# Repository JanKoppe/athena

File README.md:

# Athena

_2.1 audio crossover and headphone amplifier_

This is a work-in-progress on a simple 2.1 audio crossover using active 2nd-order RC filters, as well as a headphone amplifier based on the popular CMoy design. The PCBs have not yet been ordered and confirmed.

## Crossover frequency

The crossover frequency is set by the resistors R11-R16 and the capacitors C5-C10. Keep the values for all components the same.

Using a fixed, commonly available 100nF capacitor the following (and more) corner frequencies can be set:

Resistance | Frequency
-----------|----------
22 kOhms   |  72,34 Hz
20 kOhms   |  79,57 Hz
18 kOhms   |  88,42 Hz
16 kOhms   |  99,47 Hz
15 kOhms   | 106,10 Hz
13 kOhms   | 122,48 Hz
12 kOhms   | 132,64 Hz

## Power supply

The unit should be powered by at least 12 volts DC, but no more than 30 volts DC. More voltage will give you higher headroom for greater amplification (headphone) and high-level signal handling, though you should be able to use a regular 12 volts DC power supply for consumer line levels.

__Attention:__ The power supply must _never_ be connected to signal ground because this schematic referencing ground to VCC/2, i.e. the power supply ground is actually the negative voltage rail. Using a wall wart power supply you should not run into any issues. This avoids adding large capacitors in series on the outputs.

## Enclosure

Use Fischer Elektronik KOH-1100 and KOH-2100 case components with lasercut panels from 2mm plexiglas for the enclosure. CAD files for panel cutouts are included.

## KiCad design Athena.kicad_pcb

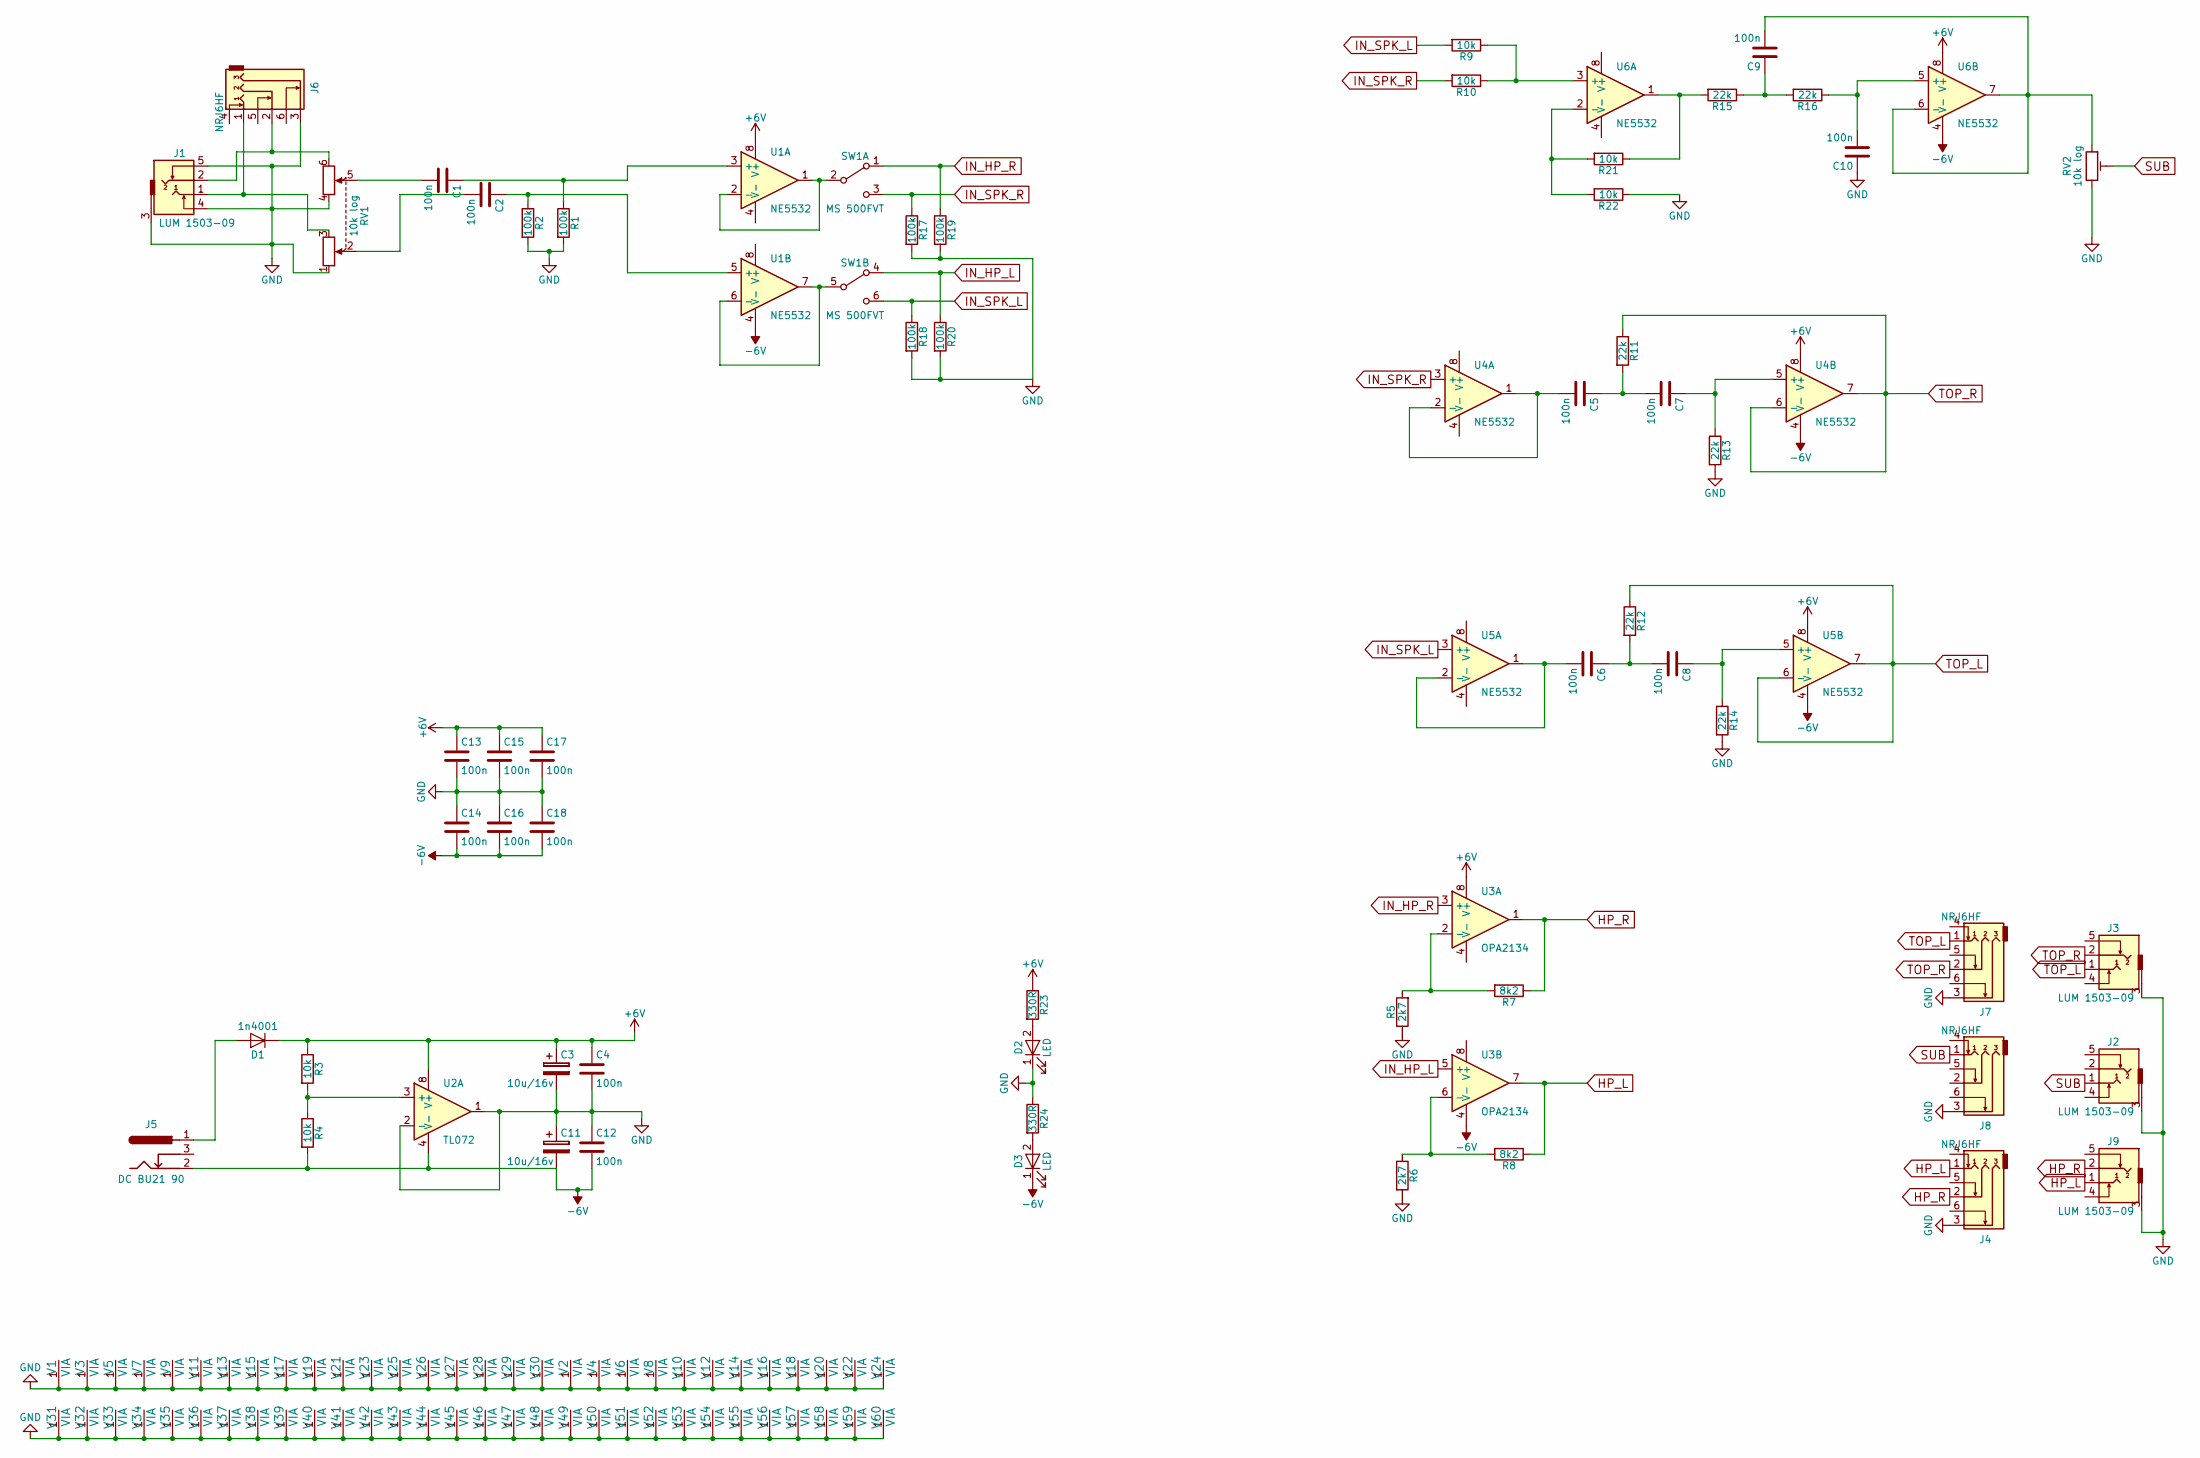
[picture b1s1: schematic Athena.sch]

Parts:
C1, C2, C4, C5, C6, C7, C8, C9, C10, C12, C13, C14, C15, C16, C17, C18: 100n; C_0805_HandSoldering
C3, C11: 10u/16v; CP_Elec_4x5.3
D1: 1n4001; D_DO-41_SOD81_P7.62mm_Horizontal
D2: LED; LED_D3.0mm_Horizontal_O3.81mm_Z6.0mm
D3: LED; LED_D3.0mm_Horizontal_O1.27mm_Z2.0mm
J1, J2, J3, J9: LUM 1503-09; LUM1503-09
J4, J6, J7, J8: NRJ6HF
J5: DC BU21 90; BARREL_JACK
R1, R2, R17, R18, R19, R20: 100k; R_0603_HandSoldering
R3, R4, R9, R10, R21, R22: 10k; R_0603_HandSoldering
R5, R6: 2k7; R_0603_HandSoldering
R7, R8: 8k2; R_0603_HandSoldering
R11, R12, R13, R14, R15, R16: 22k; R_0603_HandSoldering
R23, R24: 330R; R_0603_HandSoldering
RV1: 10k log; Potentiometer_Alps_RK09L_Double_Vertical
RV2: 10k log; Potentiometer_Trimmer_ACP_CA6v_Horizontal
SW1: MS 500FVT; MS500FVT
U1, U4, U5, U6: NE5532; SOIC-8_3.9x4.9mm_Pitch1.27mm
U2: TL072; SOIC-8_3.9x4.9mm_Pitch1.27mm
U3: OPA2134; SOIC-8_3.9x4.9mm_Pitch1.27mm
V1, V2, V3, V4, V5, V6, V7, V8, V9, V10, V11, V12, V13, V14, V15, V16, V17, V18, V19, V20, V21, V22, V23, V24, V25, V26, V27, V28, V29, V30, V31, V32, V33, V34, V35, V36, V37, V38, V39, V40, V41, V42, V43, V44, V45, V46, V47, V48, V49, V50, V51, V52, V53, V54, V55, V56, V57, V58, V59, V60: VIA; VIA-0.6

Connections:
+6V: C3.1, C4.1, C13.1, C15.1, C17.1, D1.1 (K), R3.1, R23.1, U1.8 (V+), U2.8 (V+), U3.8 (V+), U4.8 (V+), U5.8 (V+), U6.8 (V+)
-6V: C11.2, C12.2, C14.2, C16.2, C18.2, D3.1 (K), J5.2, R4.2, U1.4 (V-), U2.4 (V-), U3.4 (V-), U4.4 (V-), U5.4 (V-), U6.4 (V-)
GND: C3.2, C4.2, C10.1, C11.1, C12.1, C13.2, C14.1, C15.2, C16.1, C17.2, C18.1, D2.1 (K), J1.3, J1.4, J1.5, J2.3, J3.3, J4.3, J6.3, J7.3, J8.3, J9.3, R1.2, R2.2, R5.1, R6.2, R13.2, R14.2, R17.2, R18.2, R19.2, R20.2, R22.1, R24.1, RV1.0, RV1.1, RV1.4, RV2.3, U2.1, U2.2 (-), V1.1, V2.1, V3.1, V4.1, V5.1, V6.1, V7.1, V8.1, V9.1, V10.1, V11.1, V12.1, V13.1, V14.1, V15.1, V16.1, V17.1, V18.1, V19.1, V20.1, V21.1, V22.1, V23.1, V24.1, V25.1, V26.1, V27.1, V28.1, V29.1, V30.1, V31.1, V32.1, V33.1, V34.1, V35.1, V36.1, V37.1, V38.1, V39.1, V40.1, V41.1, V42.1, V43.1, V44.1, V45.1, V46.1, V47.1, V48.1, V49.1, V50.1, V51.1, V52.1, V53.1, V54.1, V55.1, V56.1, V57.1, V58.1, V59.1, V60.1; also elsewhere on the board
HP_L: J4.1, J9.1, R8.1, U3.7
HP_R: J4.2, J9.2, R7.1, U3.1
IN_HP_L: R20.1, SW1.4 (A), U3.5 (+)
IN_HP_R: R19.1, SW1.1 (A), U3.3 (+)
IN_SPK_L: R9.2, R18.1, SW1.6 (C), U5.3 (+)
IN_SPK_R: R10.2, R17.1, SW1.3 (C), U4.3 (+)
unnamed: C1.1, R1.1, U1.3 (+)
unnamed: C1.2, RV1.5
unnamed: C2.1, R2.1, U1.5 (+)
unnamed: C2.2, RV1.2
unnamed: C5.1, C7.2, R11.2
unnamed: C5.2, U4.1, U4.2 (-)
unnamed: C6.1, C8.2, R12.2
unnamed: C6.2, U5.1, U5.2 (-)
unnamed: C7.1, R13.1, U4.5 (+)
unnamed: C8.1, R14.1, U5.5 (+)
unnamed: C9.1, R15.1, R16.2
unnamed: C9.2, RV2.1, U6.6 (-), U6.7
unnamed: C10.2, R16.1, U6.5 (+)
unnamed: D1.2 (A), J5.1
unnamed: D2.2 (A), R23.2
unnamed: D3.2 (A), R24.2
unnamed: J1.1, J6.1, RV1.3
unnamed: J1.2, J6.2, RV1.6
unnamed: R3.2, R4.1, U2.3 (+)
unnamed: R5.2, R7.2, U3.2 (-)
unnamed: R6.1, R8.2, U3.6 (-)
unnamed: R9.1, R10.1, U6.3 (+)
unnamed: R15.2, R21.1, U6.1
unnamed: R21.2, R22.2, U6.2 (-)
unnamed: SW1.2 (B), U1.1, U1.2 (-)
unnamed: SW1.5 (B), U1.6 (-), U1.7
SUB: J2.1, J8.1, RV2.2
TOP_L: J3.1, J7.1, R12.1, U5.6 (-), U5.7
TOP_R: J3.2, J7.2, R11.1, U4.6 (-), U4.7

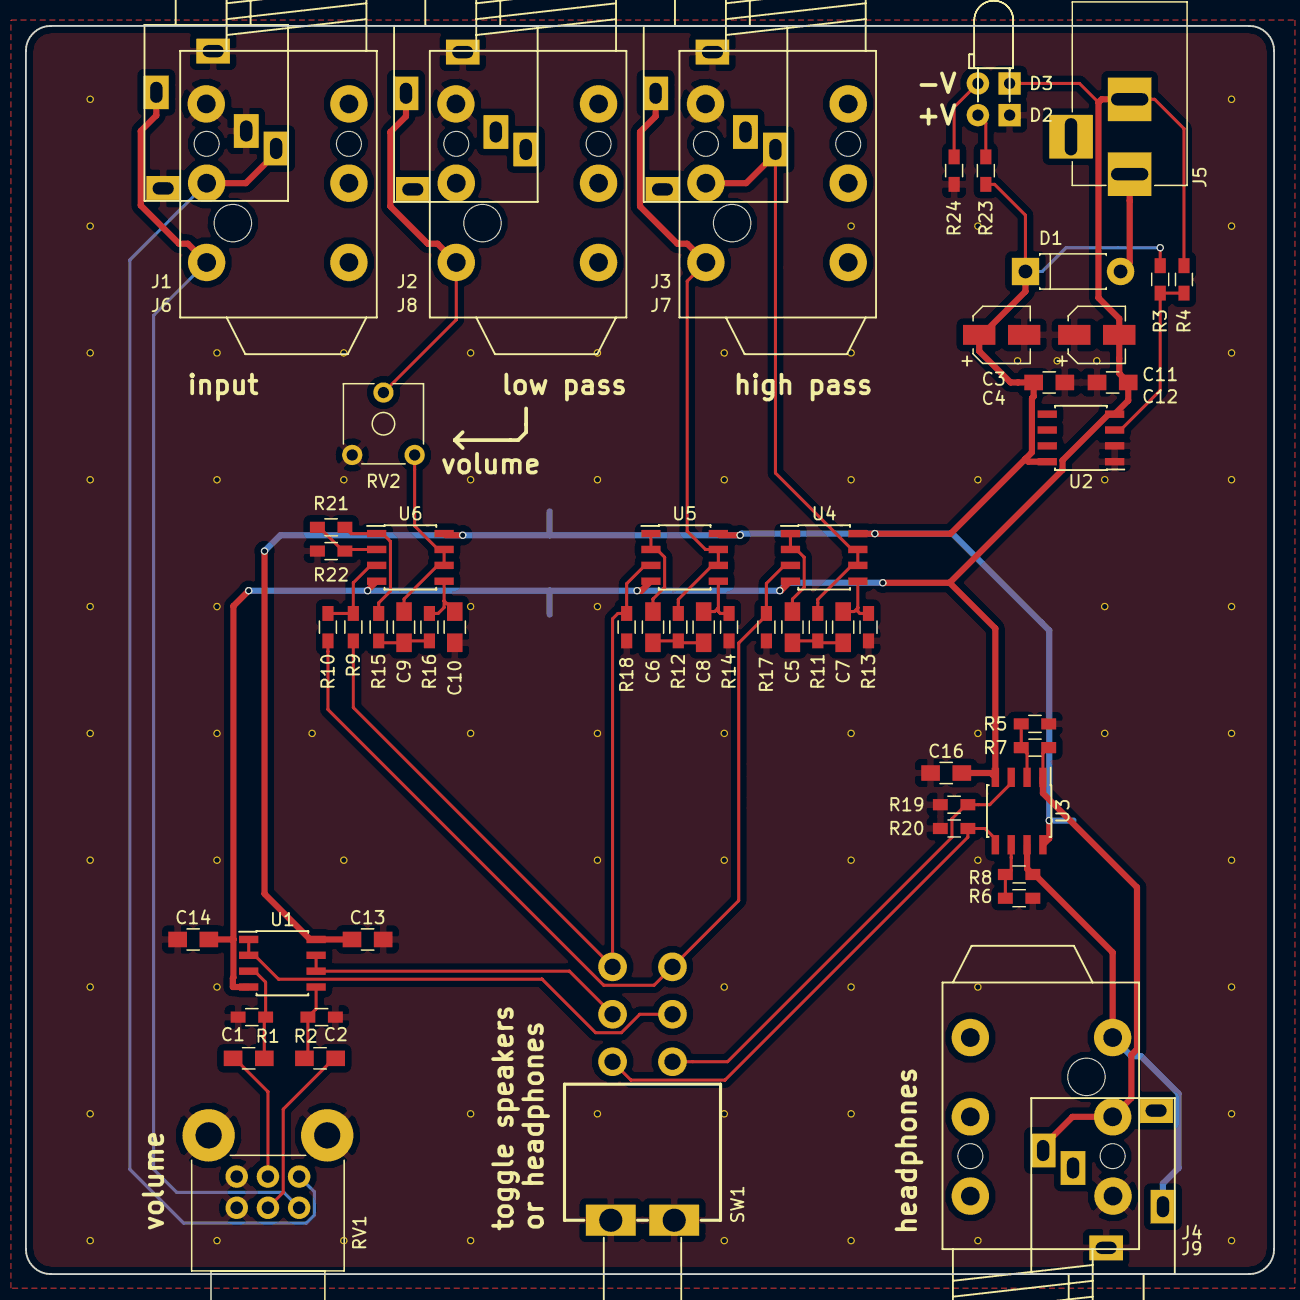
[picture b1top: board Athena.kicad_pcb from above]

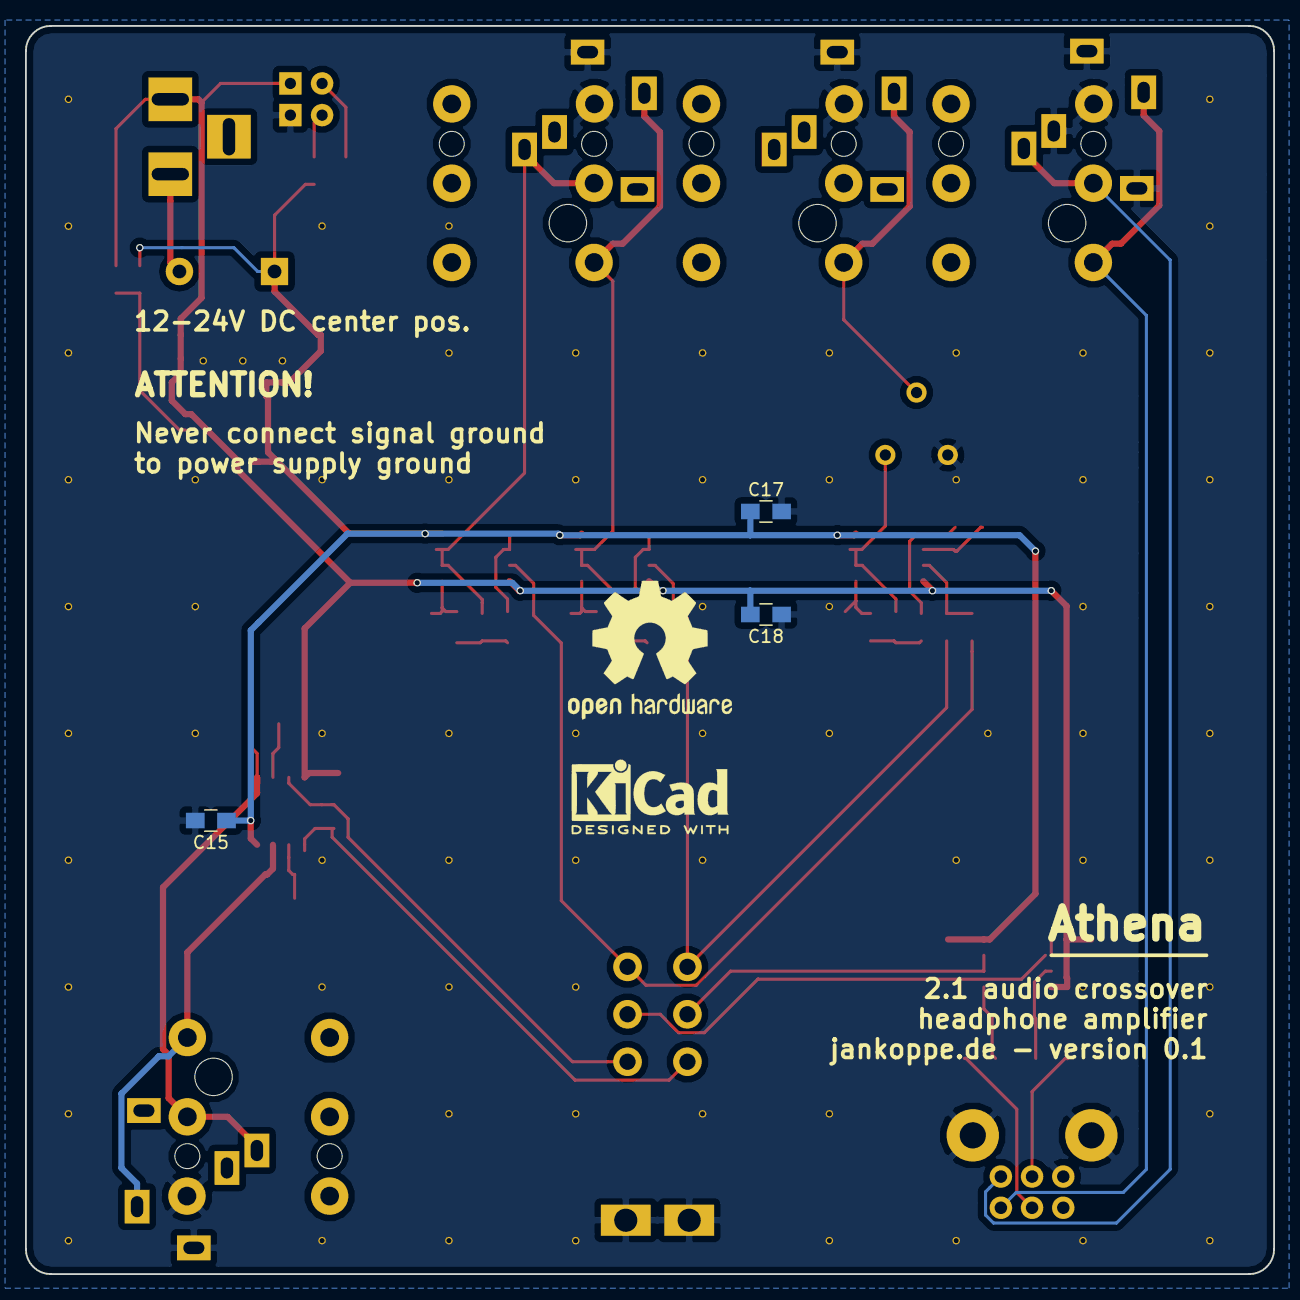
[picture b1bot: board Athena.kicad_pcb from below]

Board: 2 copper layers, 100.0 x 100.0 mm, 134 parts (3 on the bottom side), 38 nets.

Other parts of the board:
V30#2, V30#3, V30#4, V30#5, V30#6, V30#7, V30#8, V30#9, V30#10, V30#11, V30#12: VIA; VIA-0.6

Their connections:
GND: V30#2.1, V30#3.1, V30#4.1, V30#5.1, V30#6.1, V30#7.1, V30#8.1, V30#9.1, V30#10.1, V30#11.1, V30#12.1; also elsewhere on the board

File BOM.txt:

4x NE5532 SOIC-8 (U1, U4-6) (input buffer and active filters for speaker outputs)
1x OPA2134 SOIC-8 (U3) (opamp for cmoy, needs beefy output)
1x TL072 SOIC-8 (U2) (voltage rail splitter buffer)
2x 10u/16v smd electrolytic capacitor (C3, C11)
16x 100n 0805 ceramic capacitor (all other C)
6x 10k 0603 resistor (R3, R4, R9, R10, R21, R22)
6x 100k 0603 resistor (R1, R2, R17-20)
6x 22k 0603 resistor (R11-16)
2x 2k7 0603 resistor (R5, R6)
2x 8k2 0603 resistor (R7, R8)
2x 330r resistor (R23, R24) (current-limiting resistors for voltage leds)
2x 3mm LED of your choice (D2, D3) (voltage indicator leds)
1x 1n4001 diode (D1)
1x 10k single turn trimmer, flat, legs (RV2) - sub volume
1x alps RK09L12B 10k log stereo potentiometer (RV1) - main volume
1x "MS 500FVT"@reichelt.de switch, DPDT (SW1)
1x standard DC 2.1mm pcb-mount jack

Input/Output Jacks can be selected to your liking between 3.5mm and 6.3mm jacks, you will need a total of 4 jacks:
Neutrik NRJ6HF for 6.3mm and corresponding nut
Lumberg 1503-09 for 3.5mm

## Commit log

2018-02-22 version 0.1
2018-02-22 add readme
2018-02-25 changed enclosure, added power leds, resized pcb
2018-05-05 weee i need to clean up
2018-05-09 update schematic and BOM
